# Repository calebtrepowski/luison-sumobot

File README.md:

# luison-sumobot
Sumo Robot Autonomo 3kg

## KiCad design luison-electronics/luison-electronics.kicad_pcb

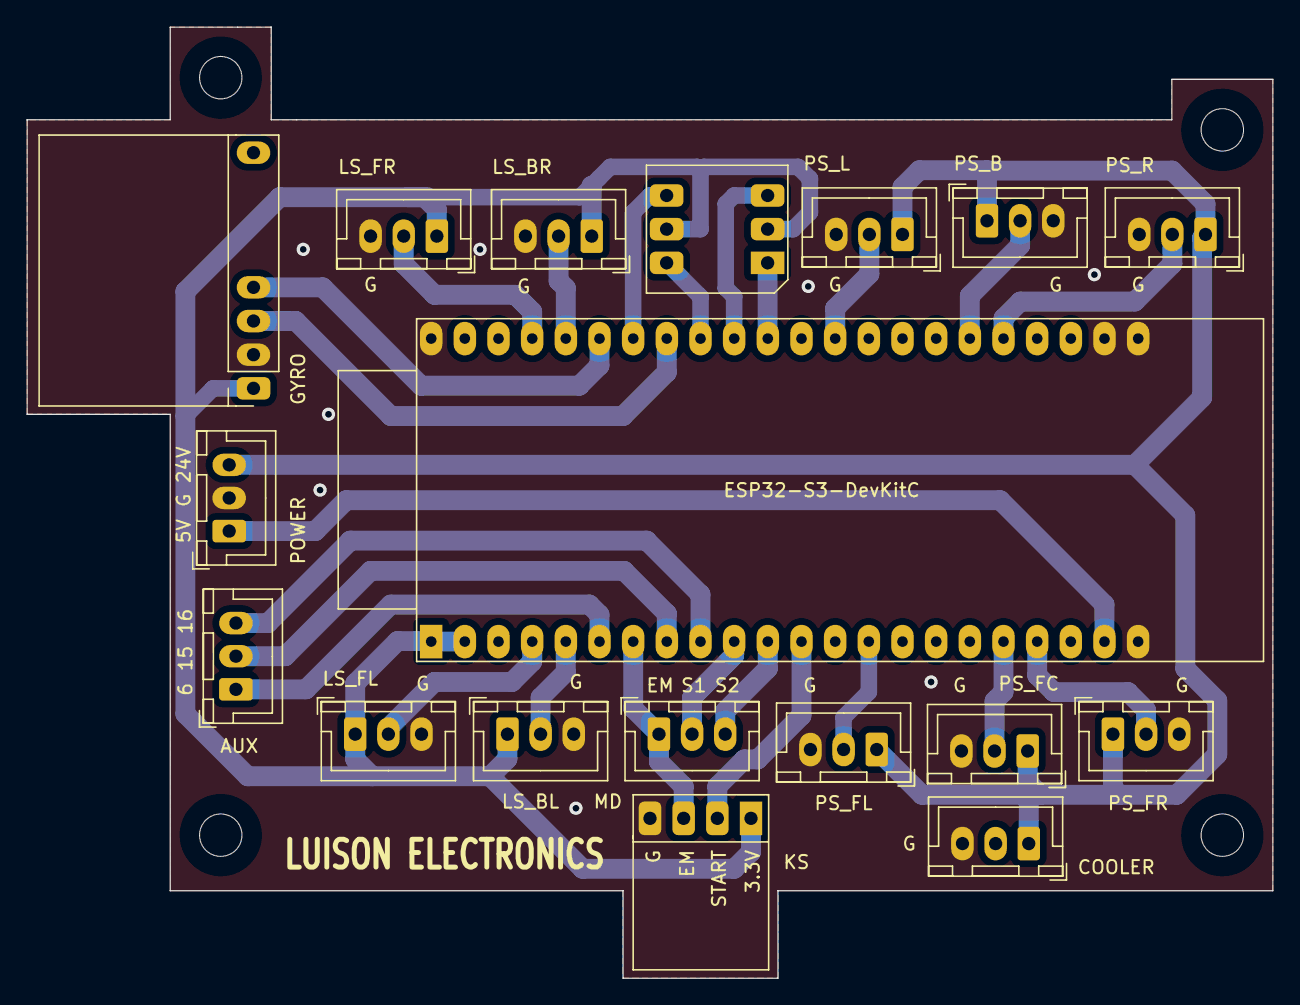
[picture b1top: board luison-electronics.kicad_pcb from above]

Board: 2 copper layers, 94.0 x 71.8 mm, 22 parts (0 on the bottom side), 27 nets.

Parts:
AUX: gpio_aux; JST_XH_B3B-XH-A_1x03_P2.50mm_Vertical
COOLER: COOLER; JST_XH_B3B-XH-A_1x03_P2.50mm_Vertical
GYRO: MPU-6050 Breakout Board; MPU6050 Breakout Board
H1, H2, H3, H4: MountingHole; MountingHole_3.2mm_M3
LS_BL: Line_Sensor; JST_XH_B3B-XH-A_1x03_P2.50mm_Vertical
LS_BR: Line_Sensor; JST_XH_B3B-XH-A_1x03_P2.50mm_Vertical
LS_FL: Line_Sensor; JST_XH_B3B-XH-A_1x03_P2.50mm_Vertical
LS_FR: Line_Sensor; JST_XH_B3B-XH-A_1x03_P2.50mm_Vertical
MD: conector_driver; JST_XH_B3B-XH-A_1x03_P2.50mm_Vertical
POWER: alimentacion_driver; JST_XH_B3B-XH-A_1x03_P2.50mm_Vertical
PS_B: Omron_E3Z-D62_2M; JST_XH_B3B-XH-A_1x03_P2.50mm_Vertical
PS_FC: Omron_E3Z-D62_2M; JST_XH_B3B-XH-A_1x03_P2.50mm_Vertical
PS_FL: Omron_E3Z-D62_2M; JST_XH_B3B-XH-A_1x03_P2.50mm_Vertical
PS_FR: Omron_E3Z-D62_2M; JST_XH_B3B-XH-A_1x03_P2.50mm_Vertical
PS_L: Omron_E3Z-D62_2M; JST_XH_B3B-XH-A_1x03_P2.50mm_Vertical
PS_R: Omron_E3Z-D62_2M; JST_XH_B3B-XH-A_1x03_P2.50mm_Vertical
SW3: EECO_Micro-Dip_3500_B02; EECO Rotary Switch
U1: ESP32-S3-DevKitC
U2: Robochallenge_KillSwitch

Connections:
+3.3V: GYRO.1 (VCC), LS_BL.1 (VCC), LS_BR.1 (VCC), LS_FL.1 (VCC), LS_FR.1 (VCC), SW3.2 (C), SW3.5 (C), U1.1 (3V3), U1.2 (3V3), U2.1 (VCC)
+5V: POWER.1 (5V), U1.21 (5V)
+24V: COOLER.1 (VCC), POWER.3 (24V), PS_B.1 (VCC), PS_FC.1 (VCC), PS_FL.1 (VCC), PS_FR.1 (VCC), PS_L.1 (VCC), PS_R.1 (VCC)
/AUX6: AUX.1 (AUX1), U1.6 (GPIO6/ADC1_CH5)
/AUX15: AUX.2 (AUX2), U1.8 (GPIO15/ADC2_CH4/32K_P)
/AUX16: AUX.3 (AUX3), U1.9 (GPIO16/ADC2_CH5/32K_N)
/KS_EM: MD.1 (KS), U1.7 (GPIO7/ADC1_CH6), U2.3 (KillSw)
/KS_START: U1.12 (GPIO8/ADC1_CH7), U2.2 (Start)
/LS_BL: LS_BL.2 (A0), U1.5 (GPIO5/ADC1_CH4)
/LS_BR: LS_BR.2 (A0), U1.40 (GPIO2/ADC1_CH1)
/LS_FL: LS_FL.2 (A0), U1.4 (GPIO4/ADC1_CH3)
/LS_FR: LS_FR.2 (A0), U1.41 (GPIO1/ADC1_CH0)
/PS_B: PS_B.2 (Signal), U1.28 (GPIO47)
/PS_FC: PS_FC.2 (Signal), U1.18 (GPIO12/ADC2_CH1)
/PS_FL: PS_FL.2 (Signal), U1.14 (GPIO46)
/PS_FR: PS_FR.2 (Signal), U1.19 (GPIO13/ADC2_CH2)
/PS_L: PS_L.2 (Signal), U1.32 (GPIO35)
/PS_R: PS_R.2 (Signal), U1.27 (GPIO21)
/RX1_MD: MD.3 (RX), U1.11 (GPIO18/ADC2_CH7)
/SCL: GYRO.3 (SCL), U1.37 (GPIO40/MTDO)
/SDA: GYRO.4 (SDA), U1.39 (GPIO42/MTMS)
/SW_P1: SW3.1, U1.34 (GPIO37)
/SW_P2: SW3.4 (P2), U1.38 (GPIO41/MTDI)
/SW_P4: SW3.3 (P4), U1.35 (GPIO38)
/SW_P8: SW3.6 (P8), U1.36 (GPIO39/MTCK)
/TX1_MD: MD.2 (TX), U1.10 (GPIO17/ADC2_CH6)
GND: COOLER.3 (GND), GYRO.2 (GND), LS_BL.3 (GND), LS_BR.3 (GND), LS_FL.3 (GND), LS_FR.3 (GND), POWER.2 (GND), PS_B.3 (GND), PS_FC.3 (GND), PS_FL.3 (GND), PS_FR.3 (GND), PS_L.3 (GND), PS_R.3 (GND), U1.22 (GND), U1.23 (GND), U1.24 (GND), U1.44 (GND), U2.4 (GND)

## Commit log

2022-09-06 Librerías, datasheet y esquemático inicial
2022-10-07 Libraries for electronic components
2022-10-07 Tests for electronic components
2022-10-07 Configuration files
2022-10-07 Test One: Interruption and strategy mixed working
2022-10-09 Add component datasheets
2022-10-09 Add libraries for electronic components
2022-10-09 Finish schematic and place components in pcb
2022-10-09 Finish dual layer PCB and generate manufacture job files
2022-10-09 Fix tracks, track widths and non-copper areas. Generate job files
2022-10-09 Add reference values and macros for IR line sensors
2022-10-09 Add turning functions for motor driver
2022-10-09 Add printStates function for debugging and macros for proximity sensors
2022-10-09 Platformio template files
2022-10-09 Add onOffInterruption file
2022-10-09 Add FSM environment and cpp file
2022-10-09 Move test files to src/tests folder
2022-10-09 Add motor indicators
2022-10-09 Nested FSM working for avoidFallFrontLeft
2022-10-10 Increase debounce time for on off control
2022-10-10 Parameterize operating speeds
2022-10-10 Add avoid fall front rigut routine
2022-10-10 Fix bounce problem when switching from on to idle
2022-10-10 Separated fsm functions in files
2022-10-10 Move fsm files to fsm folder
2022-10-10 Separate interruption routine for main program
2022-10-11 Add snippet for header files
2022-10-11 Add attack front state
2022-10-11 Fix format and details
2022-10-11 Add transition between speeds
2022-10-11 Smooth braking in idle state
2022-10-11 Fix channel error in motor library
2022-10-11 Add aim state for front left and front right
2022-10-11 Change routine speeds
2022-10-11 Aim front left and front right working
2022-10-11 Avoid fall working
2022-10-12 Aim left routine working
2022-10-12 Aim right routine working
2022-10-12 Add enable option for states
2022-10-12 Add config file
2022-10-12 Add config values for aim right and left
2022-10-12 Add aim back state
2022-10-13 Add library for zerolag motor driver
2022-10-13 Modify routines to meet zerolag driver library
2022-10-13 Add transition macros for avoid falling states
2022-10-13 Changed config values to macros
2022-10-13 Add zerolag test and check if zerolag macro
2022-10-19 Add transition macros and sort them
2022-10-19 Change attack front state body
2022-10-20 Add initial strategies (incomplete)
2022-12-08 Change aim back state body and config values
2022-12-08 Improve diagonal Kick back state and values
2022-12-08 Update attackfront state body
2022-12-08 Final config values and states for RUNIBOT competition
2022-12-08 Add bluetooth header and test
2022-12-08 Change PWM freq from 3.9k to 40k for zerolag driver
2022-12-08 Update reference values for line sensors
2022-12-08 Fix turn directions in aim states
2022-12-08 Add bluetooth debugging
2022-12-08 Activate bot and test line through bluetooth
2022-12-08 Final config values and states for NISSEI exhibition
2022-12-08 Define common behaviors for motor drivers
    Add motorDriver header with declarations of functions for motors, and
    include only this header in files.
    Set proper names to different motor drivers header files.
    Preprocessor checking for driver selected.
    Update function calls to defined behaviors.
2023-02-28 Add RGBLed module. Add common build flags in general-config
2023-02-28 Add macros for debugging
2023-02-28 Optimize digital reads on proximity sensors
2023-02-28 Add benchmark env instead of main
2023-03-06 Add datasheets of new components
2023-03-06 Add new symbols and footprints
    ESP32-S2-DevKitC-1
    JST Connector 3x01
    Custom via
    Modify pad sizes in rotary switch
2023-03-06 Add new symbols in schematic and new layout of pcb
2023-03-08 Add killlswitch library and layout pcb components
2023-03-08 Add HC-05 BT module
2023-04-12 Creacion de nueva placa
2023-04-17 asd
    asd
2023-04-18 asdf
2023-04-18 final final
2023-04-20 Update pcb with correct pins and constraints
2023-04-20 Generate gerber files
2023-04-21 Change to esp32-s3. Update pins based on new board
2023-04-21 Update dip switch to use 4 bits
2023-04-21 Update proximity read states function
2023-04-21 Make led brightness a macro, add function for custom color
2023-04-28 Optimize line sensor ADC readings
2023-04-28 Add benchmark and system info tools in debugUtils
2023-04-28 Add threshold calues for line sensors
2023-04-28 Updata gyro header file with modified library
2023-04-30 Implement bluetooth ble (btserial not tested)
2023-05-02 Implemented BLE start functionality
2023-05-05 Make debug calls unique for every debug method
2023-05-05 Change variable t to referenceTIme
2023-05-05 Add macros for line back detected, change referenceValue to thresholdValue
2023-05-05 Unify on off functions for all control methods
2023-06-20 Add Dabble BT
2023-06-20 Enable or disable gyro with macro
2023-06-20 Add Roboclaw driver functions (serial and rc)
2023-06-20 Update pin numbers based on physical convenience
2023-06-20 Update config values, add print function for const char*
2023-06-20 Add various changes
2023-06-20 Add fsm_new
2023-06-24 Add maximum retries for gyro begin
2023-06-24 Disable back line sensors. Use analogRead. Add toString for readings.
2023-06-24 Change resolution for motor speeds
2023-06-24 Change line sensor pins for physical layout
2023-06-24 Add toString for readings for prox sensors
2023-06-24 Add yellow color to rgb
2023-06-24 Check gyro status in fsm
2023-06-24 New fsm config values for metal ring, new turns
2023-06-24 Implement bluetooth with menu for all functionalities
2023-06-24 Add menu classes and test
2023-06-24 Add test all env, with bt dabble menu
2023-06-25 Use optimized analog read
2023-06-25 Give maximum priority to attack front
2023-06-25 Implement diagonal attack strategy, and different values for metal or wood ring
2023-06-25 Add calibration menu
2023-06-25 Add dipswitch reading
2023-06-26 Add wait sensors strategy
2023-06-26 Enable calibrating values for states
2023-07-06 Fix show color in rgb led, add turnoff
2023-07-06 Calibrate values for wood ring
2023-07-08 Add configvalues structs and global fsm times, add avoid back strategy
2023-10-05 Debug only front line sensors
2023-10-05 Add defaultExploringState instead of always normalSearch
2023-10-05 Add strategies and initial impulse in normal search
2023-10-05 Change to driver Meimotor
2023-10-18 Implement Open Loop Control System in 2nd core
2023-10-18 Fixed motor errors
2023-10-20 Calibrate values for new driver
2023-10-29 Change priority in line readings, add avoid bullet strategy, switch between bt and fsm in runtime
2023-11-03 Final for calibration robochallenge
